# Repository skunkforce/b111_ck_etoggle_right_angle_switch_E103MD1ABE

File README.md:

# edgy_board number b111
This design is part of the [edgy board project](https://github.com/skunkforce/edgy_boards).

# getting started
This repository uses submodules. After cloning use the command 

```$ git submodule update --init --recursive```

to pull the submodules before opening the project with kicad. 

# Tests
Tests can be found in [TESTS.md](TESTS.md)

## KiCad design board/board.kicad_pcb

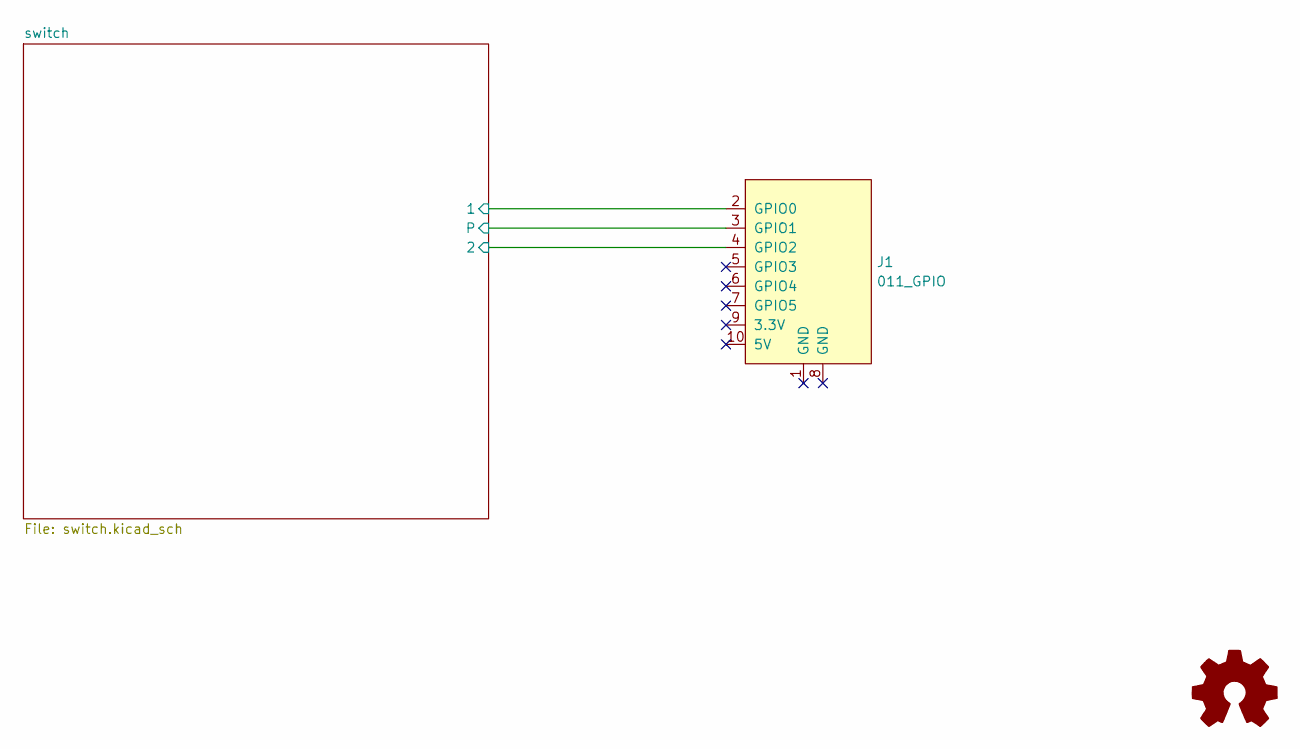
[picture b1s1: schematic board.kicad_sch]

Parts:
J1: 011_GPIO; on_edge_2x05_device
LOGO1: Logo_Open_Hardware_Small; OSHW-Symbol_6.7x6mm_SilkScreen

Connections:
/switch/1: J1.2 (GPIO0); also elsewhere on the board
/switch/2: J1.4 (GPIO2); also elsewhere on the board
/switch/P: J1.3 (GPIO1); also elsewhere on the board

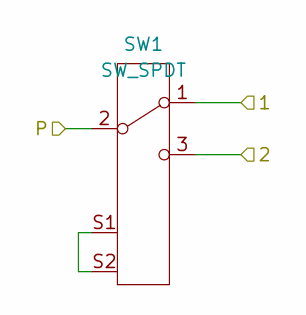
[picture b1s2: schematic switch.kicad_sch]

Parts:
SW1: SW_SPDT; SW_CuK_E103MD1ABE_SPDT_Angled; MPN E103MD1ABE; Digi-Key_PN CKN1520-ND

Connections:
/switch/1: SW1.1 (A); also elsewhere on the board
/switch/2: SW1.3 (C); also elsewhere on the board
/switch/P: SW1.2 (B); also elsewhere on the board
unnamed: SW1.S1, SW1.S2

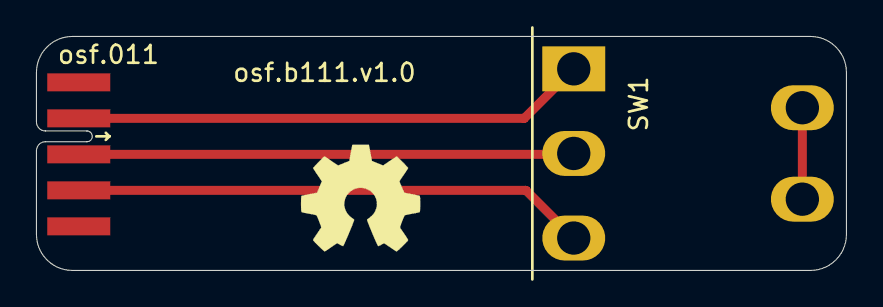
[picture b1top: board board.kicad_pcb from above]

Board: 2 copper layers, 45.0 x 13.0 mm, 3 parts (0 on the bottom side), 4 nets.

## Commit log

2023-03-14 initial
